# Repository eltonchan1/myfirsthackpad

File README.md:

# myfirsthackpad

myfirsthackpad is a space themed 3 key macropad with 5 SK6812 MINI-E LEDs.

It is used as a media playback controller to go back, pause, and go next.

## Features:

- 3 Keys
- 5 SK6812 MINI-E LEDs (3 for underglow and 2 that just glow)

## CAD Model:
Everything fits together using 5 M3 Bolts and heatset inserts. 4 for the case, one for the PCB. 

It has 2 separate printed pieces: the base where the PCB sits, and the top cover. 

This was made in Onshape.

## PCB
This is my PCB made in KiCad. The silkscreen was imported from my drawings on photoshop.

Schematic:

PCB:

## Firmware Overview
This hackpad uses [QMK](https://qmk.fm/) firmware for everything. 

- The 4 keys currently act as a media playback controller through macros.

## BOM:
Here should be everything you need to make this hackpad

- 3x Cherry MX Switches
- 3x DSA Keycaps
- 4x M3x5x4 Heatset inserts
- 4x M3x16mm screws
- 5x SK6812 MINI-E LEDs
- 1x XIAO RP2040
- 1x Case (2 printed parts)

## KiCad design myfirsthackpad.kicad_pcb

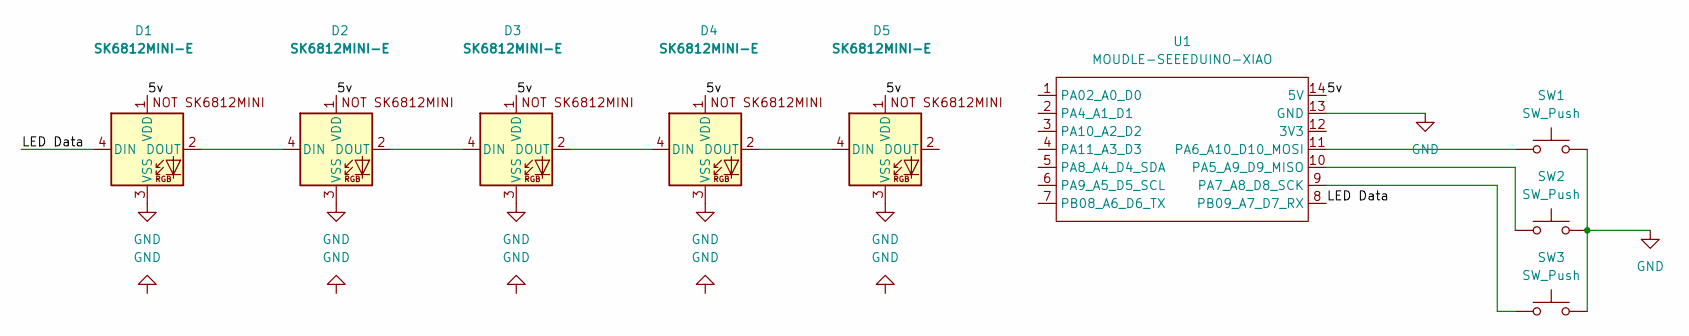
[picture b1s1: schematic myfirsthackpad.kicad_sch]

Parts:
D1, D2, D3, D4, D5: SK6812MINI-E; MX_SK6812MINI-E_REV
SW1, SW2, SW3: SW_Push; SW_Cherry_MX_1.00u_PCB
U1: MOUDLE-SEEEDUINO-XIAO; XIAO-Generic-Hybrid-14P-2.54-21X17.8MM

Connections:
/5v: D1.1 (VDD), D2.1 (VDD), D3.1 (VDD), D4.1 (VDD), D5.1 (VDD), U1.14 (5V)
/LED Data: D1.4 (DIN), U1.8 (PB09_A7_D7_RX)
GND: D1.3 (VSS), D2.3 (VSS), D3.3 (VSS), D4.3 (VSS), D5.3 (VSS), SW1.2, SW2.2, SW3.2, U1.13 (GND)
unnamed: D1.2 (DOUT), D2.4 (DIN)
unnamed: D2.2 (DOUT), D3.4 (DIN)
unnamed: D3.2 (DOUT), D4.4 (DIN)
unnamed: D4.2 (DOUT), D5.4 (DIN)
unnamed: SW2.1, U1.10 (PA5_A9_D9_MISO)
unnamed: SW1.1, U1.11 (PA6_A10_D10_MOSI)
unnamed: SW3.1, U1.9 (PA7_A8_D8_SCK)

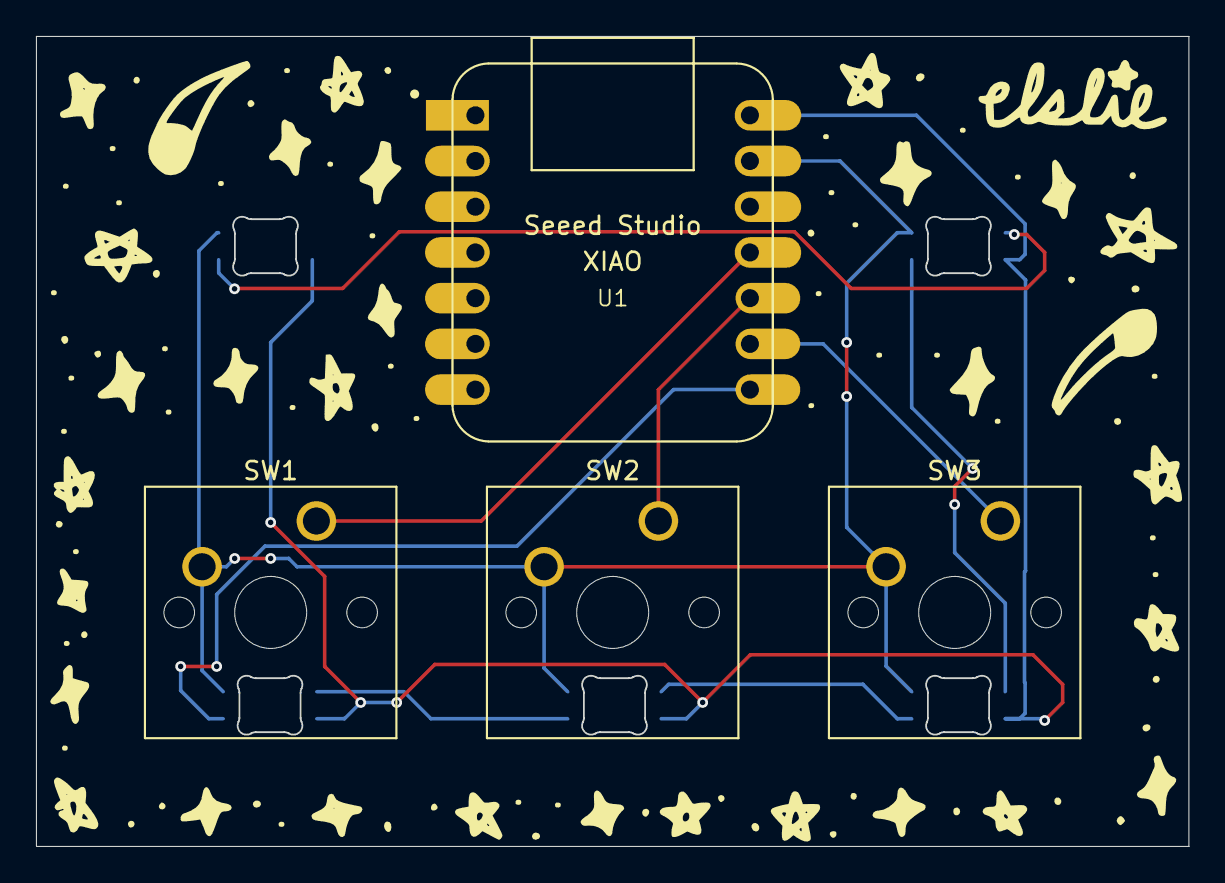
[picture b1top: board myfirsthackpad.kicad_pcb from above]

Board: 2 copper layers, 64.0 x 45.0 mm, 9 parts (0 on the bottom side), 10 nets.
